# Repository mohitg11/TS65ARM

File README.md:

# TS65 - ARM Based
The Split 65% Keyboard - ARM Based

This is a custom 65% style keyboard that is split in the middle to provide a more ergonomic option whilest not being drastically different from the standard stagger used on keyboards

#Features
- Open Source Design
- Fully Programmable Keys
- Split design for better ergonomics, while maintaining the currently "standard" keyboard layout
- PCBs and case designed so that the two sides can be connected into standard 65% without split
- Infinite layers
- Alps & Cherry (PCB and Plate) switches supported
- PCB mount stabs supported
- All keys individually lit. LED on top to maintain compatibility with the few backlit keysets out there
- 18 RGB SMD LEDs on the bottom of the PCB for under/side glow
- 3 indicator LEDs
- Individual resistors for the LEDs not required as it uses a dedicated LED driver
- Either side (Left or right) can be connected to the PC
- USB 3.0 Type A and USB Type C are used.
- Using larger (0805) capacitors and resistors so it is easy to hand-solder
- SMD (SOD-123) diodes only

#Layout options
- Split backspace
- Split left shift
- ISO support
- Off-center capslock
- 2.75 and 1.75 right shift
- Lots of options for bottom row

In the below image you can see the different options available, the top four rows represent the four rows of th keyboard and the options for the final keyboard row is represented by the remaining rows in the image.

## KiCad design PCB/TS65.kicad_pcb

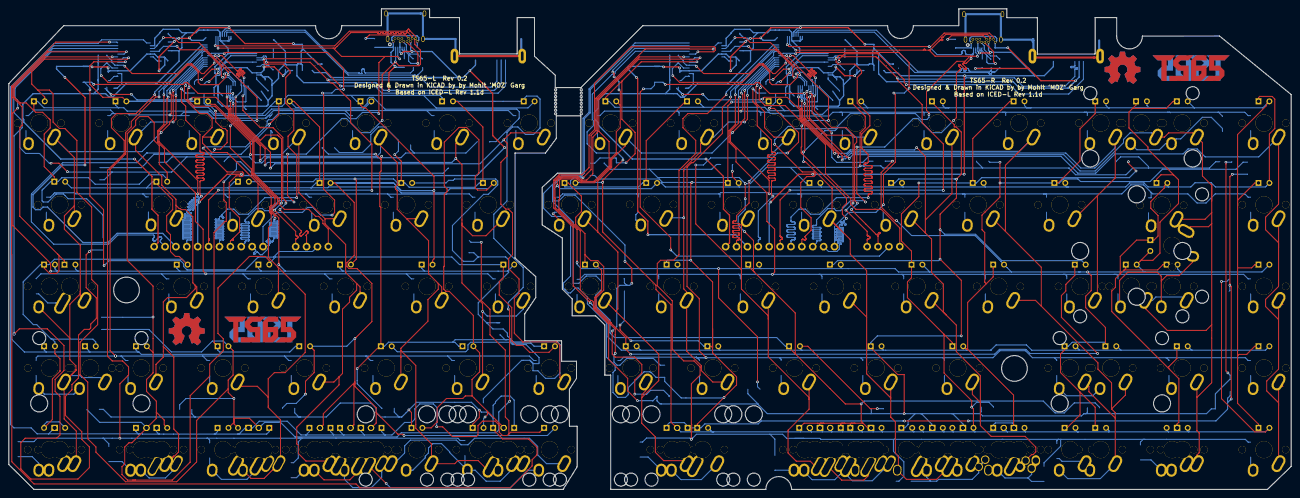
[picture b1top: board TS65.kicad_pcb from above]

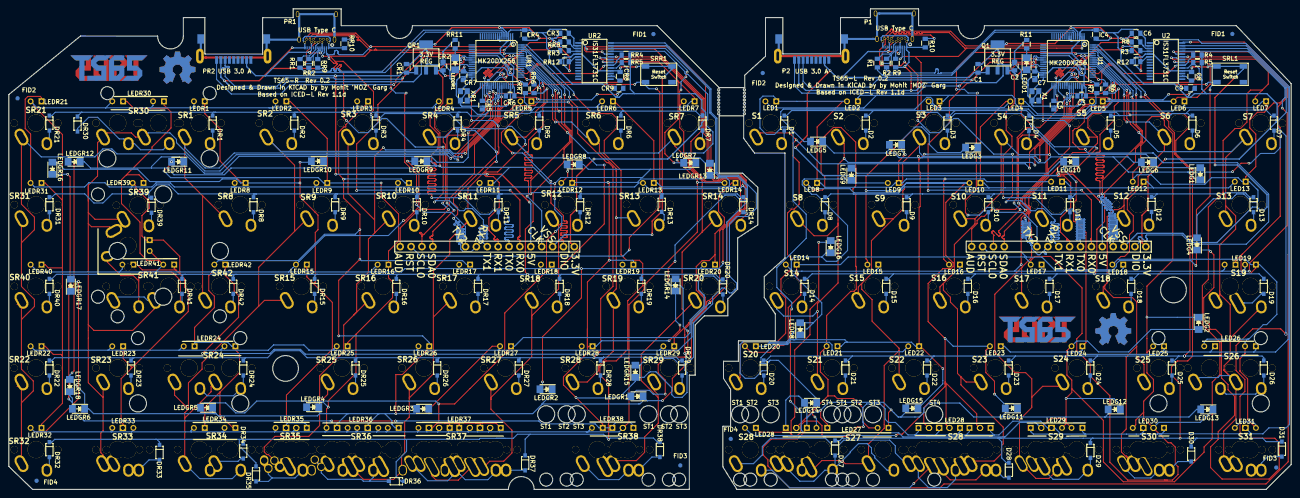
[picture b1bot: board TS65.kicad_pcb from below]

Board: 2 copper layers, 299.2 x 112.1 mm, 419 parts (179 on the bottom side), 180 nets.

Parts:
BREAKHOLES1, BREAKHOLES2: BreakHoles
C1, C2, C3: 1uF; SMD_0805
C4, C5, C6, C7, C8: 0.1uF; SMD_0805
C9: 0.22uF; SMD_0805
CR1, CR2, CR3: 1uF; SMD_0805
CR4, CR5, CR6, CR7, CR8: 0.1uF; SMD_0805
CR9: 0.22uF; SMD_0805
D1, D2, D3, D4, D5, D6, D7, D8, D9, D10, D11, D12, D13, D14, D15, D16, D17, D18, D19, D20, D21, D22, D23, D24, D25, D26, D27, D28, D29, D30, D31: DIODE; SOD123-DIODE
DR1, DR2, DR3, DR4, DR5, DR6, DR7, DR8, DR9, DR10, DR11, DR12, DR13, DR14, DR15, DR16, DR17, DR18, DR19, DR20, DR21, DR22, DR23, DR24, DR25, DR26, DR27, DR28, DR29, DR30, DR31, DR32, DR33, DR34, DR35, DR36, DR37, DR38, DR39, DR40, DR41, DR42: DIODE; SOD123-DIODE
FID1, FID1#2, FID2, FID2#2, FID3, FID3#2, FID4, FID4#2: FID
HOLE1, HOLE1#2: FID
LED1, LED2, LED3, LED4, LED5, LED6, LED7, LED8, LED9, LED10, LED11, LED12, LED13, LED14, LED15, LED16, LED17, LED18, LED19, LED19_2, LED20, LED21, LED22, LED23, LED24, LED25, LED26, LED26_2, LED27, LED27_2, LED27_3, LED27_4, LED28, LED28_2, LED28_3, LED28_4, LED28_5, LED28_6, LED28_7, LED29, LED29_2, LED29_3, LED29_4, LED30, LED30_2, LED30_3, LED31, LED31_2: LED; INSW_LEDS_REG
LEDD1: LED; LED_1206
LEDDR1: LED; LED_1206
LEDG1, LEDG2, LEDG3, LEDG4, LEDG5, LEDG6, LEDG7, LEDG8, LEDG9, LEDG10, LEDG11, LEDG12, LEDG13, LEDG14, LEDG15, LEDG16: LED; LED_1206
LEDGR1, LEDGR2, LEDGR3, LEDGR4, LEDGR5, LEDGR6, LEDGR7, LEDGR8, LEDGR9, LEDGR10, LEDGR11, LEDGR12, LEDGR13, LEDGR14, LEDGR15, LEDGR16, LEDGR17, LEDGR18: LED; LED_1206
LEDR1, LEDR2, LEDR3, LEDR4, LEDR5, LEDR6, LEDR7, LEDR8, LEDR9, LEDR10, LEDR11, LEDR12, LEDR13, LEDR14, LEDR15, LEDR16, LEDR17, LEDR18, LEDR19, LEDR20, LEDR21, LEDR22, LEDR23, LEDR24, LEDR24_2, LEDR25, LEDR26, LEDR27, LEDR28, LEDR29, LEDR30, LEDR30_2, LEDR31, LEDR32, LEDR33, LEDR33_2, LEDR34, LEDR34_2, LEDR35, LEDR35_2, LEDR35_3, LEDR36, LEDR36_2, LEDR36_3, LEDR36_4, LEDR36_5, LEDR37, LEDR37_2, LEDR37_3, LEDR37_4, LEDR37_5, LEDR37_6, LEDR37_7, LEDR38, LEDR38_2, LEDR38_3, LEDR39, LEDR40, LEDR41, LEDR41_2, LEDR41_3, LEDR42: LED; INSW_LEDS_REG
LOGO1, LOGO1#2, LOGO2, LOGO2#2: LOGO; TS65-LOGO
LOGO3, LOGO3#2, LOGO3#3, LOGO4: OSHW
P1: USB_TYPE_C; USB_TYPE_C_HYBRID
P2: USB3_AFEMALE; USB3_AFEMALE_MOD
P3: CONN_17; HEADER_1x17
PR1: USB_TYPE_C; USB_TYPE_C_HYBRID
PR2: USB3_AFEMALE; USB3_AFEMALE_MOD
PR3: CONN_17; HEADER_1x17
Q1: 3.3V REG IC; SOT-223
QR1: 3.3V REG IC; SOT-223
R1, R2: 33; SMD_0805
R3, R4, R5: 4.7k; SMD_0805
R6, R7: 100; SMD_0805
R8: 100k; SMD_0805
R9, R10: 5.1k; SMD_0805
R11: 1k; SMD_0805
R12: 20k; SMD_0805
RR1, RR2: 33; SMD_0805
RR3, RR4, RR5: 4.7k; SMD_0805
RR6, RR7: 100; SMD_0805
RR8: 100k; SMD_0805
RR9, RR10: 5.1k; SMD_0805
RR11: 1k; SMD_0805
RR12: 20k; SMD_0805
S1, S2, S3, S4, S5, S6, S7, S8, S9, S10, S11, S12, S13, S14, S15, S16, S17, S18, S19, S19_2, S20, S21, S22, S23, S24, S25, S26, S26_2, S27, S27_2, S27_3, S27_4, S28, S28_2, S28_3, S28_4, S28_5, S28_6, S28_7, S29, S29_2, S29_3, S29_4, S30, S30_2, S30_3, S31, S31_2: SW; MXALPS
SR1, SR2, SR3, SR4, SR5, SR6, SR7, SR8, SR9, SR10, SR11, SR12, SR13, SR14, SR15, SR16, SR17, SR18, SR19, SR20, SR21, SR22, SR23, SR24, SR24_2, SR25, SR26, SR27, SR28, SR29, SR30, SR30_2, SR31, SR32, SR33, SR33_2, SR34, SR34_2, SR35_3, SR36_2, SR36_3, SR36_4, SR36_5, SR37, SR37_2, SR37_3, SR37_4, SR37_5, SR37_6, SR37_7, SR38, SR38_2, SR38_3, SR39, SR40, SR41, SR41_2, SR41_3, SR42: SW; MXALPS
SR35, SR35_2, SR36: SW; MXALPS2
SRL1: TAC_SWITCH; TACT_5.2x5.2
SRR1: TAC_SWITCH; TACT_5.2x5.2
STAB1, STAB3, STAB5: MX_225
STAB2: MX_275
STAB4: MX_225_Plated; MX_225
STABR1, STABR7: MX_275
STABR2: MX_225
STABR3, STABR5: MX_200
STABR4: MX_225_Plated; MX_225
STABR6: MX_275_Plated; MX_275
U1: MK20DX256VLH7; LQFP64
U2: IS31FL3731; SSOP-28
UR1: MK20DX256VLH7; LQFP64
UR2: IS31FL3731; SSOP-28
X1: CRYSTAL; NX3225SA
XR1: CRYSTAL; NX3225SA

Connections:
+5V: C1.1, CR1.1, P1.A4, P1.A9, P1.B4, P1.B9, P2.1, P3.5, PR1.A4, PR1.A9, PR1.B4, PR1.B9, PR2.1, PR3.5, Q1.1, QR1.1
/ledmatrix/CA1: LED1.2, LED2.1, LED3.1, LED4.1, LED5.1, LED6.2, LED10.2, LED15.2, LED23.2, LED28.2, LED28_2.2, LED28_3.2, LED28_4.2, LED28_5.2, LED28_6.2, LED28_7.2, LEDG1.1, LEDG6.2, LEDG11.2, U2.21
/ledmatrix/CA2: LED1.1, LED2.2, LED7.2, LED8.1, LED9.1, LED11.2, LED16.2, LED24.2, LED29.2, LED29_2.2, LED29_3.2, LED29_4.2, LEDG2.1, LEDG3.1, LEDG7.2, LEDG12.2, U2.22
/ledmatrix/CA3: LED3.2, LED6.1, LED7.1, LED12.2, LED13.1, LED14.1, LED17.2, LED20.2, LED25.2, LED30.2, LED30_2.2, LED30_3.2, LEDG2.2, LEDG4.1, LEDG13.2, U2.23
/ledmatrix/CA4: LED4.2, LED8.2, LED10.1, LED11.1, LED12.1, LED13.2, LED18.2, LED19.1, LED19_2.1, LED21.2, LED26.2, LED26_2.2, LED27.2, LED27_2.2, LED27_3.2, LED27_4.2, LED31.2, LED31_2.2, LEDG5.1, U2.24
/ledmatrix/CA5: LED5.2, LED9.2, LED14.2, LED15.1, LED16.1, LED17.1, LED18.1, LED19.2, LED19_2.2, LED22.2, LEDG8.1, LEDG9.2, LEDG14.2, LEDG16.2, U2.25
/ledmatrix/CA6: LED20.1, LED21.1, LED22.1, LEDG1.2, LEDG3.2, LEDG4.2, LEDG5.2, LEDG6.1, LEDG7.1, LEDG8.2, LEDG10.2, LEDG15.2, U2.26
/ledmatrix/CA7: LED23.1, LED24.1, LED25.1, LED26.1, LED26_2.1, LEDG9.1, LEDG10.1, U2.27
/ledmatrix/CA8: LED27.1, LED27_2.1, LED27_3.1, LED27_4.1, LEDG11.1, LEDG12.1, LEDG13.1, LEDG14.1, LEDG15.1, U2.28
/ledmatrix/CA9: LED28.1, LED28_2.1, LED28_3.1, LED28_4.1, LED28_5.1, LED28_6.1, LED28_7.1, LED29.1, LED29_2.1, LED29_3.1, LED29_4.1, LED30.1, LED30_2.1, LED30_3.1, LED31.1, LED31_2.1, LEDG16.1, U2.1
/ledmatrixR/CA1: LEDGR7.1, LEDGR13.1, LEDR1.2, LEDR2.2, LEDR3.2, LEDR4.2, LEDR5.2, LEDR6.2, LEDR7.1, LEDR21.2, LEDR22.1, LEDR30.2, LEDR30_2.2, LEDR31.1, LEDR32.1, LEDR40.1, UR2.21
/ledmatrixR/CA2: LEDGR1.1, LEDGR8.1, LEDGR14.1, LEDR8.2, LEDR9.2, LEDR10.2, LEDR11.2, LEDR12.2, LEDR13.2, LEDR21.1, LEDR23.1, LEDR31.2, LEDR33.1, LEDR33_2.1, LEDR39.2, LEDR41.1, LEDR41_2.1, LEDR41_3.1, UR2.22
/ledmatrixR/CA3: LEDGR2.1, LEDGR9.1, LEDGR15.1, LEDR15.2, LEDR16.2, LEDR17.2, LEDR18.2, LEDR19.2, LEDR20.2, LEDR24.1, LEDR24_2.1, LEDR30.1, LEDR30_2.1, LEDR34.1, LEDR34_2.1, LEDR39.1, LEDR40.2, LEDR41.2, LEDR41_2.2, LEDR41_3.2, UR2.23
/ledmatrixR/CA4: LEDGR3.1, LEDGR10.1, LEDGR16.1, LEDR1.1, LEDR8.1, LEDR15.1, LEDR22.2, LEDR23.2, LEDR24.2, LEDR24_2.2, LEDR25.2, LEDR26.2, LEDR27.2, LEDR28.2, LEDR29.2, LEDR35.1, LEDR35_2.1, LEDR35_3.1, UR2.24
/ledmatrixR/CA5: LEDGR4.1, LEDGR11.1, LEDGR17.1, LEDR2.1, LEDR9.1, LEDR14.2, LEDR16.1, LEDR25.1, LEDR32.2, LEDR33.2, LEDR33_2.2, LEDR34.2, LEDR34_2.2, LEDR35.2, LEDR35_2.2, LEDR35_3.2, LEDR36.2, LEDR36_2.2, LEDR36_3.2, LEDR36_4.2, LEDR36_5.2, LEDR37.2, LEDR37_2.2, LEDR37_3.2, LEDR37_4.2, LEDR37_5.2, LEDR37_6.2, LEDR37_7.2, LEDR38.2, LEDR38_2.2, LEDR38_3.2, UR2.25
/ledmatrixR/CA6: LEDGR1.2, LEDGR2.2, LEDGR3.2, LEDGR4.2, LEDGR5.2, LEDGR6.2, LEDGR12.1, LEDGR18.1, LEDR3.1, LEDR7.2, LEDR10.1, LEDR17.1, LEDR26.1, LEDR36.1, LEDR36_2.1, LEDR36_3.1, LEDR36_4.1, LEDR36_5.1, LEDR42.2, UR2.26
/ledmatrixR/CA7: LEDGR5.1, LEDGR7.2, LEDGR8.2, LEDGR9.2, LEDGR10.2, LEDGR11.2, LEDGR12.2, LEDR4.1, LEDR11.1, LEDR18.1, LEDR27.1, LEDR37.1, LEDR37_2.1, LEDR37_3.1, LEDR37_4.1, LEDR37_5.1, LEDR37_6.1, LEDR37_7.1, UR2.27
/ledmatrixR/CA8: LEDGR6.1, LEDGR13.2, LEDGR14.2, LEDGR15.2, LEDGR16.2, LEDGR17.2, LEDGR18.2, LEDR5.1, LEDR12.1, LEDR19.1, LEDR28.1, LEDR38.1, LEDR38_2.1, LEDR38_3.1, UR2.28
/ledmatrixR/CA9: LEDR6.1, LEDR13.1, LEDR14.1, LEDR20.1, LEDR29.1, LEDR42.1, UR2.1
/mcu/AUD: C9.2, P3.17
/mcu/GND: P1.0, P2.10
/mcu/INTB: R3.2, U1.40, U2.4
/mcu/MCU_RESET: C5.1, P3.16, SRL1.2, U1.34
/mcu/PTA5: LEDD1.1, U1.27
/mcu/PTB18: S1.1, S20.1, U1.41
/mcu/PTB19: S2.1, S8.1, S14.1, S21.1, U1.42
/mcu/PTC0: S3.1, S9.1, S15.1, S22.1, S27.1, S27_2.1, S27_4.1, U1.43
/mcu/PTC9: S4.1, S10.1, S16.1, S23.1, S28.1, S28_2.1, S28_4.1, S28_5.1, S28_6.1, S28_7.1, U1.54
/mcu/PTC10: S5.1, S11.1, S17.1, S24.1, S29.1, S29_3.1, S29_4.1, U1.55
/mcu/PTC11: S6.1, S12.1, S18.1, S25.1, S30.1, S30_2.1, U1.56
/mcu/PTD0: S7.1, S13.1, S19.1, S19_2.2, S26.1, S26_2.1, S31.1, S31_2.1, U1.57
/mcu/PTD1: D1.2, D2.2, D3.2, D4.2, D5.2, D6.2, D7.2, U1.58
/mcu/PTD4: D8.2, D9.2, D10.2, D11.2, D12.2, D13.2, U1.61
/mcu/PTD5: D14.2, D15.2, D16.2, D17.2, D18.2, D19.2, U1.62
/mcu/PTD6: D20.2, D21.2, D22.2, D23.2, D24.2, D25.2, D26.2, U1.63
/mcu/PTD7: D27.2, D28.2, D29.2, D30.2, D31.2, U1.64
/mcu/RX0: P2.6, P3.6, U1.23
/mcu/RX1: P1.A3, P1.B3, P3.8, U1.2
/mcu/RX2: P3.10, U1.59
/mcu/SCL0: P3.15, R4.2, U1.35, U2.20
/mcu/SDA0: P3.14, R5.2, U1.36, U2.19
/mcu/SDB: R8.2, U1.39, U2.3
/mcu/SWD_CLK: P3.4, R6.2
/mcu/SWD_DIO: P3.2, R7.2
/mcu/TX0: P2.5, P3.7, U1.24
/mcu/TX1: P1.A2, P1.B2, P3.9, U1.1
/mcu/TX2: P3.11, U1.60
/mcu/USB_DM: R1.2, U1.6
/mcu/USB_DP: R2.2, U1.5
/mcuR/AUD: CR9.2, PR3.17
/mcuR/GNDR: PR1.0, PR2.10
/mcuR/INTB: RR3.2, UR1.40, UR2.4
/mcuR/MCU_RESET: CR5.1, PR3.16, SRR1.2, UR1.34
/mcuR/PTA5: LEDDR1.1, UR1.27
/mcuR/PTB2: SR21.1, SR22.1, SR31.1, SR32.1, SR40.1, UR1.37
/mcuR/PTB3: SR23.1, SR30.1, SR30_2.1, SR33.1, SR33_2.1, SR39.1, SR41.1, SR41_2.1, SR41_3.1, UR1.38
/mcuR/PTB18: SR1.1, SR8.1, SR42.1, UR1.41
/mcuR/PTB19: SR2.1, SR9.1, SR15.1, SR24.1, SR24_2.1, SR34.1, SR34_2.1, UR1.42
/mcuR/PTC0: SR3.1, SR10.1, SR16.1, SR25.1, SR35_2.1, SR35_3.1, UR1.43
/mcuR/PTC9: SR4.1, SR11.1, SR17.1, SR26.1, SR36.1, SR36_3.1, SR36_4.1, SR36_5.1, UR1.54
/mcuR/PTC10: SR5.1, SR12.1, SR18.1, SR27.1, SR37_3.1, SR37_5.1, SR37_6.1, UR1.55
/mcuR/PTC11: SR6.1, SR13.1, SR19.1, SR28.1, UR1.56
/mcuR/PTD0: SR7.1, SR14.1, SR20.1, SR29.1, SR38_2.1, SR38_3.1, UR1.57
/mcuR/PTD1: DR1.2, DR2.2, DR3.2, DR4.2, DR5.2, DR6.2, DR7.2, DR21.2, DR30.2, UR1.58
/mcuR/PTD4: DR8.2, DR9.2, DR10.2, DR11.2, DR12.2, DR13.2, DR14.2, DR31.2, DR39.2, UR1.61
/mcuR/PTD5: DR15.2, DR16.2, DR17.2, DR18.2, DR19.2, DR20.2, DR40.2, DR41.2, DR42.2, UR1.62
/mcuR/PTD6: DR22.2, DR23.2, DR24.2, DR25.2, DR26.2, DR27.2, DR28.2, DR29.2, UR1.63
/mcuR/PTD7: DR32.2, DR33.2, DR34.2, DR35.2, DR36.2, DR37.2, DR38.2, UR1.64
/mcuR/RX0: PR2.6, PR3.6, UR1.23
/mcuR/RX1: PR1.A3, PR1.B3, PR3.8, UR1.2
/mcuR/RX2: PR3.10, UR1.59
/mcuR/SCL0: PR3.15, RR4.2, UR1.35, UR2.20
/mcuR/SDA0: PR3.14, RR5.2, UR1.36, UR2.19
/mcuR/SDB: RR8.2, UR1.39, UR2.3
/mcuR/SWD_CLK: PR3.4, RR6.2
/mcuR/SWD_DIO: PR3.2, RR7.2
/mcuR/TX0: PR2.5, PR3.7, UR1.24
/mcuR/TX1: PR1.A2, PR1.B2, PR3.9, UR1.1
/mcuR/TX2: PR3.11, UR1.60
/mcuR/USB_DM: RR1.2, UR1.6
/mcuR/USB_DP: RR2.2, UR1.5
unnamed: C8.1, U2.16
unnamed: C9.1, U2.17
unnamed: CR8.1, UR2.16
unnamed: CR9.1, UR2.17
unnamed: D1.1, S1.2
unnamed: D2.1, S2.2
unnamed: D3.1, S3.2
unnamed: D4.1, S4.2
unnamed: D5.1, S5.2
unnamed: D6.1, S6.2
unnamed: D7.1, S7.2
unnamed: D8.1, S8.2
unnamed: D9.1, S9.2
unnamed: D10.1, S10.2
unnamed: D11.1, S11.2
unnamed: D12.1, S12.2
unnamed: D13.1, S13.2
unnamed: D14.1, S14.2
unnamed: D15.1, S15.2
unnamed: D16.1, S16.2
unnamed: D17.1, S17.2
unnamed: D18.1, S18.2
unnamed: D19.1, S19_2.1
unnamed: D20.1, S20.2
unnamed: D21.1, S21.2
unnamed: D22.1, S22.2
unnamed: D23.1, S23.2
unnamed: D24.1, S24.2
unnamed: D25.1, S25.2
unnamed: D26.1, S26.2, S26_2.2
unnamed: D27.1, S27.2, S27_2.2, S27_3.2, S27_4.2
unnamed: D28.1, S28.2, S28_2.2, S28_3.2, S28_4.2, S28_7.2
unnamed: D29.1, S29.2, S29_2.2, S29_3.2
unnamed: D30.1, S30.2, S30_2.2, S30_3.2
unnamed: D31.1, S31.2, S31_2.2
unnamed: DR1.1, SR1.2
unnamed: DR2.1, SR2.2
unnamed: DR3.1, SR3.2
unnamed: DR4.1, SR4.2
unnamed: DR5.1, SR5.2
unnamed: DR6.1, SR6.2
unnamed: DR7.1, SR7.2
unnamed: DR8.1, SR8.2
unnamed: DR9.1, SR9.2
unnamed: DR10.1, SR10.2
unnamed: DR11.1, SR11.2
unnamed: DR12.1, SR12.2
unnamed: DR13.1, SR13.2
unnamed: DR14.1, SR14.2
unnamed: DR15.1, SR15.2
unnamed: DR16.1, SR16.2
unnamed: DR17.1, SR17.2
unnamed: DR18.1, SR18.2
unnamed: DR19.1, SR19.2
unnamed: DR20.1, SR20.2
unnamed: DR21.1, SR21.2
unnamed: DR22.1, SR22.2
unnamed: DR23.1, SR23.2
unnamed: DR24.1, SR24.2, SR24_2.2
unnamed: DR25.1, SR25.2
unnamed: DR26.1, SR26.2
unnamed: DR27.1, SR27.2
unnamed: DR28.1, SR28.2
unnamed: DR29.1, SR29.2
unnamed: DR30.1, SR30.2, SR30_2.2
unnamed: DR31.1, SR31.2
unnamed: DR32.1, SR32.2
unnamed: DR33.1, SR33.2, SR33_2.2
unnamed: DR34.1, SR34.2, SR34_2.2
unnamed: DR35.1, SR35.2, SR35_2.2, SR35_3.2
unnamed: DR36.1, SR36.2, SR36_2.2, SR36_3.2, SR36_4.2
unnamed: DR37.1, SR37.2, SR37_2.2, SR37_4.2, SR37_5.2, SR37_6.2, SR37_7.2
unnamed: DR38.1, SR38.2, SR38_2.2, SR38_3.2
unnamed: DR39.1, SR39.2
unnamed: DR40.1, SR40.2
unnamed: DR41.1, SR41.2, SR41_2.2, SR41_3.2
unnamed: DR42.1, SR42.2
unnamed: LEDD1.2, R11.1
unnamed: LEDDR1.2, RR11.1
unnamed: P1.A5, R9.2
unnamed: P1.A6, P1.B6, R2.1
unnamed: P1.A7, P1.B7, R1.1
unnamed: P1.B5, R10.1
unnamed: PR1.A5, RR9.2
unnamed: PR1.A6, PR1.B6, RR2.1
unnamed: PR1.A7, PR1.B7, RR1.1
unnamed: PR1.B5, RR10.1
unnamed: R6.1, U1.22
unnamed: R7.1, U1.25
unnamed: R12.1, U2.6
unnamed: RR6.1, UR1.22
unnamed: RR7.1, UR1.25
unnamed: RR12.1, UR2.6
unnamed: U1.32, X1.1
unnamed: U1.33, X1.3
unnamed: UR1.32, XR1.1
unnamed: UR1.33, XR1.3
VDD: C2.1, C3.2, C4.1, C6.1, C7.1, CR2.1, CR3.2, CR4.1, CR6.1, CR7.1, P3.1, PR3.1, Q1.3, QR1.3, R3.1, R4.1, R5.1, RR3.1, RR4.1, RR5.1, U1.3, U1.7, U1.8, U1.21, U1.30, U1.48, U2.2, UR1.3, UR1.7, UR1.8, UR1.21, UR1.30, UR1.48, UR2.2
VSS: C1.2, C2.2, C3.1, C4.2, C5.2, C6.2, C7.2, C8.2, CR1.2, CR2.2, CR3.1, CR4.2, CR5.2, CR6.2, CR7.2, CR8.2, P1.A1, P1.A12, P1.B1, P1.B12, P2.4, P3.3, PR1.A1, PR1.A12, PR1.B1, PR1.B12, PR2.4, PR3.3, Q1.2, QR1.2, R8.1, R9.1, R10.2, R11.2, R12.2, RR8.1, RR9.1, RR10.2, RR11.2, RR12.2, SRL1.3, SRL1.4, SRR1.3, SRR1.4, U1.4, U1.31, U1.47, U2.5, U2.18, UR1.4, UR1.31, UR1.47, UR2.5, UR2.18, X1.2, X1.4, XR1.2, XR1.4

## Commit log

2016-02-01 :lollipop: Added .gitattributes & .gitignore files
2016-02-01 Initial Upload
2016-02-07 Case V1
2016-02-08 Rev 0.2 - Combined left and right sides
2016-02-10 Case updated to PCB Rev 0.2
2016-02-25 PCB version 0.3
    Case still to be updated to Rev 0.3
2016-03-29 General cleanup
